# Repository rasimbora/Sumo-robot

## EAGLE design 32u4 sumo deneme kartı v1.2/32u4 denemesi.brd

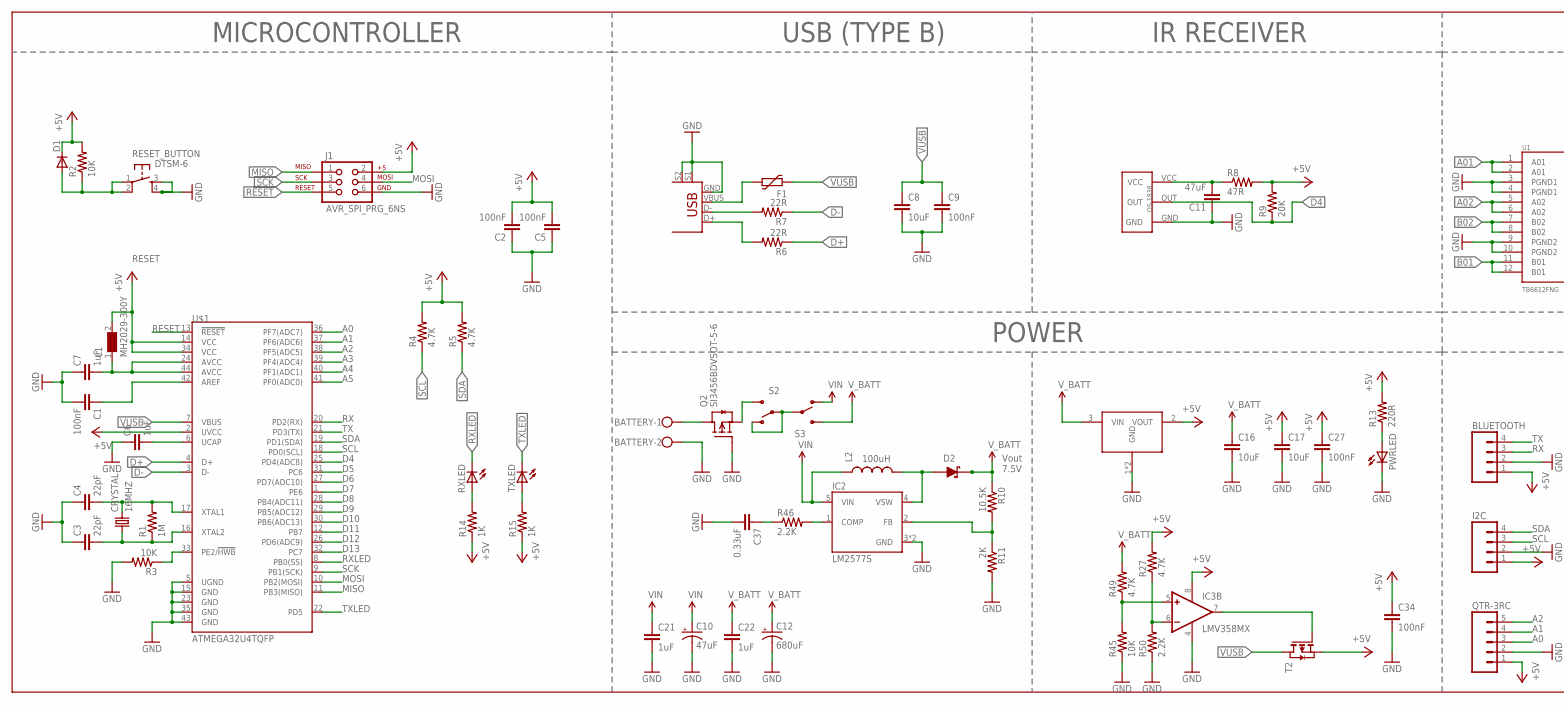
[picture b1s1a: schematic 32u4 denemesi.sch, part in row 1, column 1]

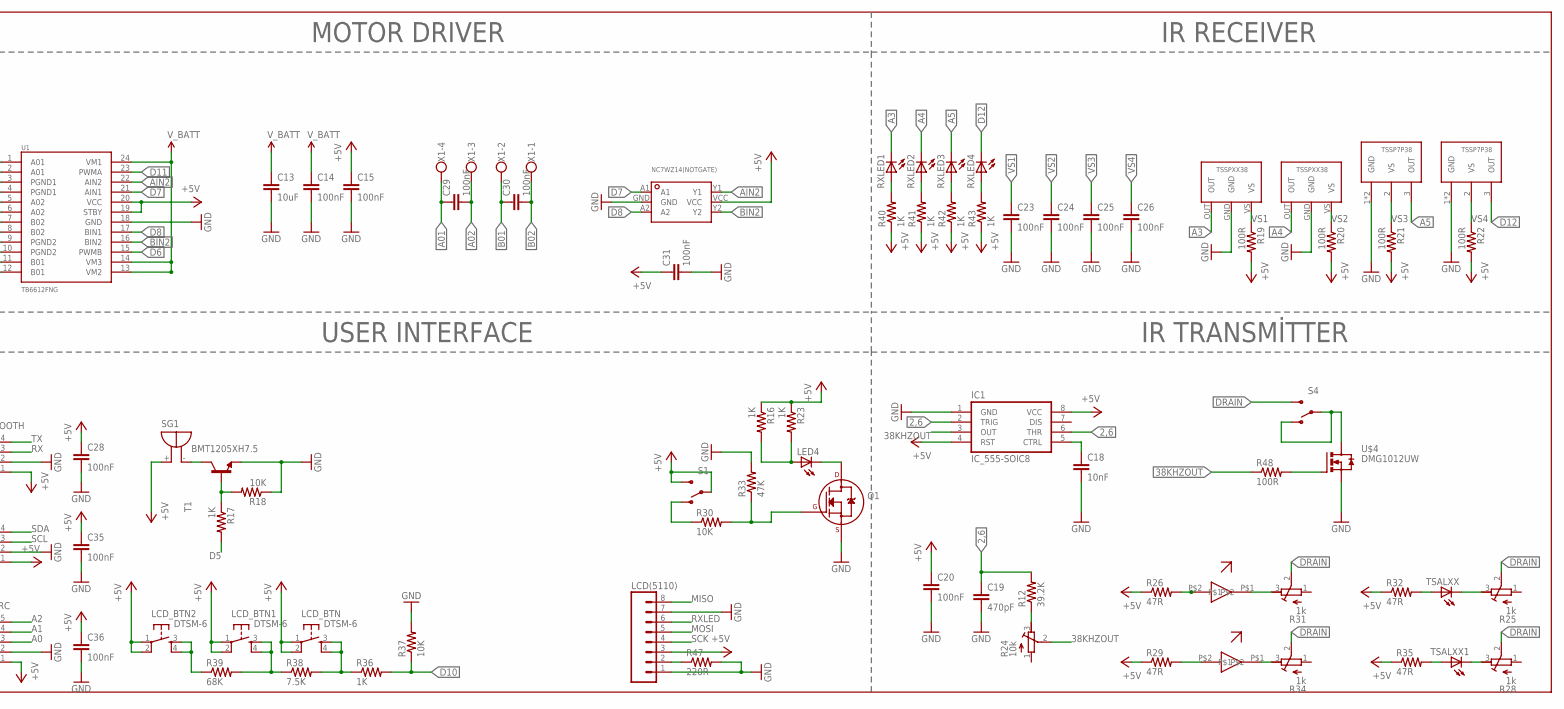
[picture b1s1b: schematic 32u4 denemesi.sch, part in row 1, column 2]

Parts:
BATTERY: W237-102
BLUETOOTH: M04PTH; 1X04
C1, C2, C5, C9, C14, C15, C20, C23, C24, C25, C26, C27, C28, C29, C30, C31, C34, C35, C36: 100nF; 1206
C3, C4: 22pF; 1206
C6, C7, C21, C22: 1uF; 1206
C8, C13, C16, C17: 10uF; 1206
C10: 47uF; NIPPON_F80
C11: 47uF; 1206
C12: 680uF; PANASONIC_G
C18: 10nF; 1206
C19: 470pF; 1206
C37: 0.33uF; 1206
CRYSTAL: 16MHZ; CRYSTAL-SMD-5X3
D1: DIODE-MINIMELF; MINIMELF
D2: D_SCHOTTKYA; SMA
F1: FUSE_PTC-0805; PTC0805
I2C: M04PTH; 1X04
IC1: IC_555-SOIC8; SOIC-8
IC2: LM2577S; TO263-5
IC3: LMV358MX; SO08
J1: AVR_SPI_PRG_6NS; 2X3-NS
L1: MH2029-300Y; 0805
L2: INDUCTORPWR; CDRH125
LCD(5110): M081X08; 1X08
LCD_BTN, LCD_BTN1, LCD_BTN2: DTSM-6
LED4: LEDCHIPLED_0805; CHIPLED_0805
PWRLED: LEDCHIPLED_0805; CHIPLED_0805
Q1: 2N7000_SOT23; SOT-23
Q2: SI3456BDVSOT-5-6; SOT23-6
QTR-3RC: M05PTH; 1X05
R1: 1M; 0805
R2, R3, R18, R30, R37, R45: 10K; 0805
R4, R5, R27, R49: 4.7K; 0805
R6, R7: 22R; 0805
R8, R26, R29, R32, R35: 47R; 0805
R9: 20K; 0805
R10: 10.5K; 0805
R11: 2K; 0805
R12: 39.2K; 0805
R13, R47: 220R; 0805
R14, R15, R16, R17, R23, R36, R40, R41, R42, R43: 1K; 0805
R19, R20, R21, R22, R48: 100R; 0805
R24: 10k; RTRIM3296W
R25, R28, R31, R34: 1k; RTRIM3296W
R33: 47K; 0805
R38: 7.5K; 0805
R39: 68K; 0805
R46, R50: 2.2K; 0805
RESET_BUTTON: DTSM-6
RXLED, RXLED1, RXLED2, RXLED3, RXLED4: LEDCHIPLED_0805; CHIPLED_0805
S1, S2, S3, S4: SWITCH-SPDTPTH; SWITCH-SPDT
SG1: BMT1205XH7.5
T1: MMBT2222ALT1-NPN-SOT23-BEC; SOT23-BEC
T2: PMOSSOT23; SOT-23
TSALXX, TSALXX1: LED5MM
TXLED: LEDCHIPLED_0805; CHIPLED_0805
U1: TB6612FNG; SSOP24
U$1: ATMEGA32U4TQFP; SPARKFUN-DIGITALIC_TQFP44
U$2: USB+SHIELD; USB-B-PTH
U$3: OS-1838
U$4: DMG1012UW; SOT323
U$5: NCP1117; SOT223
U$6, U$7: TSSP7P38
U$8, U$9: TSSPXX38
U$10: NC7WZ14(NOTGATE); SC-70-6
U$11, U$12: IRLED
X1: W237-4

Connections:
2,6: C19.1, IC1.2 (TRIG), IC1.6 (THR), R12.2
38KHZOUT: IC1.3 (OUT), R24.2 (S), R48.1
+5V: BLUETOOTH.1, C2.2, C5.2, C15.1, C17.1, C20.1, C27.1, C28.1, C31.1, C34.1, C35.1, C36.1, D1.C, I2C.1, IC1.4 (RST), IC1.8 (VCC), IC3.8 (V+), J1.2, L1.2, LCD(5110).3, LCD_BTN.1, LCD_BTN.2, LCD_BTN1.1, LCD_BTN1.2, LCD_BTN2.1, LCD_BTN2.2, QTR-3RC.1, R2.2, R4.2, R5.2, R8.2, R9.2, R13.2, R14.1, R15.1, R16.1, R19.2, R20.2, R21.2, R22.2, R23.1, R26.1, R27.2, R29.1, R32.1, R35.1, R40.1, R41.1, R42.1, R43.1, S1.2, S1.3 (S), SG1.+, T2.2 (S), U1.19 (STBY), U1.20 (VCC), U$1.2 (UVCC), U$1.14 (VCC), U$1.34 (VCC), U$5.2 (VOUT), U$10.VCC
A0: QTR-3RC.3, U$1.36 (PF7(ADC7))
A1: QTR-3RC.4, U$1.37 (PF6(ADC6))
A01: C29.1, U1.1 (A01), U1.2 (A01), X1.4
A2: QTR-3RC.5, U$1.38 (PF5(ADC5))
A02: C29.2, U1.5 (A02), U1.6 (A02), X1.3
A3: RXLED1.C, U$1.39 (PF4(ADC4)), U$9.OUT
A4: RXLED2.C, U$1.40 (PF1(ADC1)), U$8.OUT
A5: RXLED3.C, U$1.41 (PF0(ADC0)), U$6.3 (OUT)
AIN2: U1.22 (AIN2), U$10.Y1
B01: C30.1, U1.11 (B01), U1.12 (B01), X1.2
B02: C30.2, U1.7 (B02), U1.8 (B02), X1.1
BIN2: U1.16 (BIN2), U$10.Y2
CTRL: C18.1, IC1.5 (CTRL)
D4: R9.1, U$1.25 (PD4(ADC8)), U$3.OUT
D5: R17.2, U$1.31 (PC6)
D6: U1.15 (PWMB), U$1.27 (PD7(ADC10))
D7: U1.21 (AIN1), U$1.1 (PE6), U$10.A1
D8: U1.17 (BIN1), U$1.28 (PB4(ADC11)), U$10.A2
D9: U$1.29 (PB5(ADC12))
D10: R36.2, R37.1, U$1.30 (PB6(ADC13))
D11: U1.23 (PWMA), U$1.12 (PB7)
D12: RXLED4.C, U$1.26 (PD6(ADC9)), U$7.3 (OUT)
D13: U$1.32 (PC7)
D+: R6.1, U$1.4 (D+)
D-: R7.1, U$1.3 (D-)
DRAIN: R25.2 (S), R28.2 (S), R31.2 (S), R34.2 (S), S4.3 (S)
GND: BATTERY.2, BLUETOOTH.2, C1.2, C2.1, C3.1, C4.1, C5.1, C6.1, C7.1, C8.2, C9.2, C10.-, C11.1, C12.-, C13.2, C14.2, C15.2, C16.2, C17.2, C18.2, C19.2, C20.2, C21.2, C22.2, C23.2, C24.2, C25.2, C26.2, C27.2, C28.2, C31.2, C34.2, C35.2, C36.2, C37.2, I2C.2, IC1.1 (GND), IC2.3 (GND), IC2.6 (GND), IC3.4 (V-), J1.6, LCD(5110).1, LCD(5110).7, PWRLED.C, Q1.2 (S), Q2.3 (G), QTR-3RC.2, R3.2, R11.2, R18.1, R33.2, R37.2, R45.1, R47.2, R50.1, RESET_BUTTON.3, RESET_BUTTON.4, T1.E, U1.3 (PGND1), U1.4 (PGND1), U1.9 (PGND2), U1.10 (PGND2), U1.18 (GND), U$1.5 (UGND), U$1.15 (GND), U$1.23 (GND), U$1.35 (GND), U$1.43 (GND), U$2.GND, U$2.S1, U$2.S2, U$3.GND, U$4.2 (S), U$5.1 (GND), U$5.4 (GND), U$6.1 (GND), U$6.4 (GND), U$7.1 (GND), U$7.4 (GND), U$8.GND, U$9.GND, U$10.GND
MISO: J1.1, LCD(5110).8, U$1.11 (PB3(MISO))
MOSI: J1.4, LCD(5110).5, U$1.10 (PB2(MOSI))
unnamed: C7.2, L1.1, U$1.24 (AVCC), U$1.44 (AVCC)
unnamed: C1.1, U$1.42 (AREF)
unnamed: C6.2, U$1.6 (UCAP)
unnamed: C4.2, CRYSTAL.3 (2), R1.2, U$1.17 (XTAL1)
unnamed: C3.2, CRYSTAL.1, R1.1, U$1.16 (XTAL2)
unnamed: F1.2, U$2.VBUS
unnamed: R3.1, U$1.33 (PE2/!HWB)
unnamed: LCD_BTN2.3, LCD_BTN2.4, R39.1
unnamed: R7.2, U$2.D-
unnamed: R6.2, U$2.D+
unnamed: IC3.5 (+IN), R45.2, R49.1
unnamed: C11.2, R8.1, U$3.VCC
unnamed: PWRLED.A, R13.1
unnamed: IC2.2 (FB), R10.2, R11.1
unnamed: R48.2, U$4.1 (G)
unnamed: LCD_BTN.3, LCD_BTN.4, R36.1, R38.2
unnamed: LCD_BTN1.3, LCD_BTN1.4, R38.1, R39.2
unnamed: R40.2, RXLED1.A
unnamed: R14.2, RXLED.A
unnamed: R15.2, TXLED.A
unnamed: LED4.A, R16.2, R23.2
unnamed: R17.1, R18.2, T1.B
unnamed: IC3.6 (-IN), R27.1, R50.2
unnamed: SG1.-, T1.C
unnamed: IC3.7 (OUT), T2.3 (G)
unnamed: R12.1, R24.3 (A)
unnamed: R41.2, RXLED2.A
unnamed: S4.1 (O), S4.2, U$4.3 (D)
unnamed: R25.3 (A), TSALXX.K (C)
unnamed: R32.2, TSALXX.A
unnamed: LED4.C, Q1.3 (D)
unnamed: R28.3 (A), TSALXX1.K (C)
unnamed: R35.2, TSALXX1.A
unnamed: R30.1, S1.1 (O)
unnamed: Q1.1 (G), R30.2, R33.1
unnamed: R31.3 (A), U$11.P$1
unnamed: R26.2, U$11.P$2
unnamed: R34.3 (A), U$12.P$1
unnamed: R29.2, U$12.P$2
unnamed: BATTERY.1, Q2.1 (D), Q2.2 (D), Q2.5 (D), Q2.6 (D)
unnamed: R42.2, RXLED3.A
unnamed: Q2.4 (S), S2.3 (S)
unnamed: IC2.1 (COMP), R46.2
unnamed: C37.1, R46.1
unnamed: S2.1 (O), S2.2, S3.2
unnamed: LCD(5110).2, R47.1
unnamed: R43.2, RXLED4.A
RESET: D1.A, J1.5, R2.1, RESET_BUTTON.1, RESET_BUTTON.2, U$1.13 (!RESET)
RX: BLUETOOTH.3, U$1.20 (PD2(RX))
RXLED: LCD(5110).6, RXLED.C, U$1.8 (PB0(SS))
SCK: J1.3, LCD(5110).4, U$1.9 (PB1(SCK))
SCL: I2C.3, R4.1, U$1.18 (PD0(SCL))
SDA: I2C.4, R5.1, U$1.19 (PD1(SDA))
TX: BLUETOOTH.4, U$1.21 (PD3(TX))
TXLED: TXLED.C, U$1.22 (PD5)
VIN: C10.+, C21.1, IC2.5 (VIN), L2.1, S3.1 (O)
VS1: C23.1, R19.1, U$9.VS
VS2: C24.1, R20.1, U$8.VS
VS3: C25.1, R21.1, U$6.2 (VS)
VS4: C26.1, R22.1, U$7.2 (VS)
VSW: D2.2 (A), IC2.4 (VSW), L2.2
VUSB: C8.1, C9.1, F1.1, T2.1 (D), U$1.7 (VBUS)
V_BATT: C12.+, C13.1, C14.1, C16.1, C22.1, D2.1 (C), R10.1, R49.2, S3.3 (S), U1.13 (VM2), U1.14 (VM3), U1.24 (VM1), U$5.3 (VIN)

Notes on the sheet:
MICROCONTROLLER
USB (TYPE B)
POWER
IR RECEIVER
MOTOR DRIVER
USER INTERFACE
IR TRANSMİTTER
Vout 7.5V
100uH

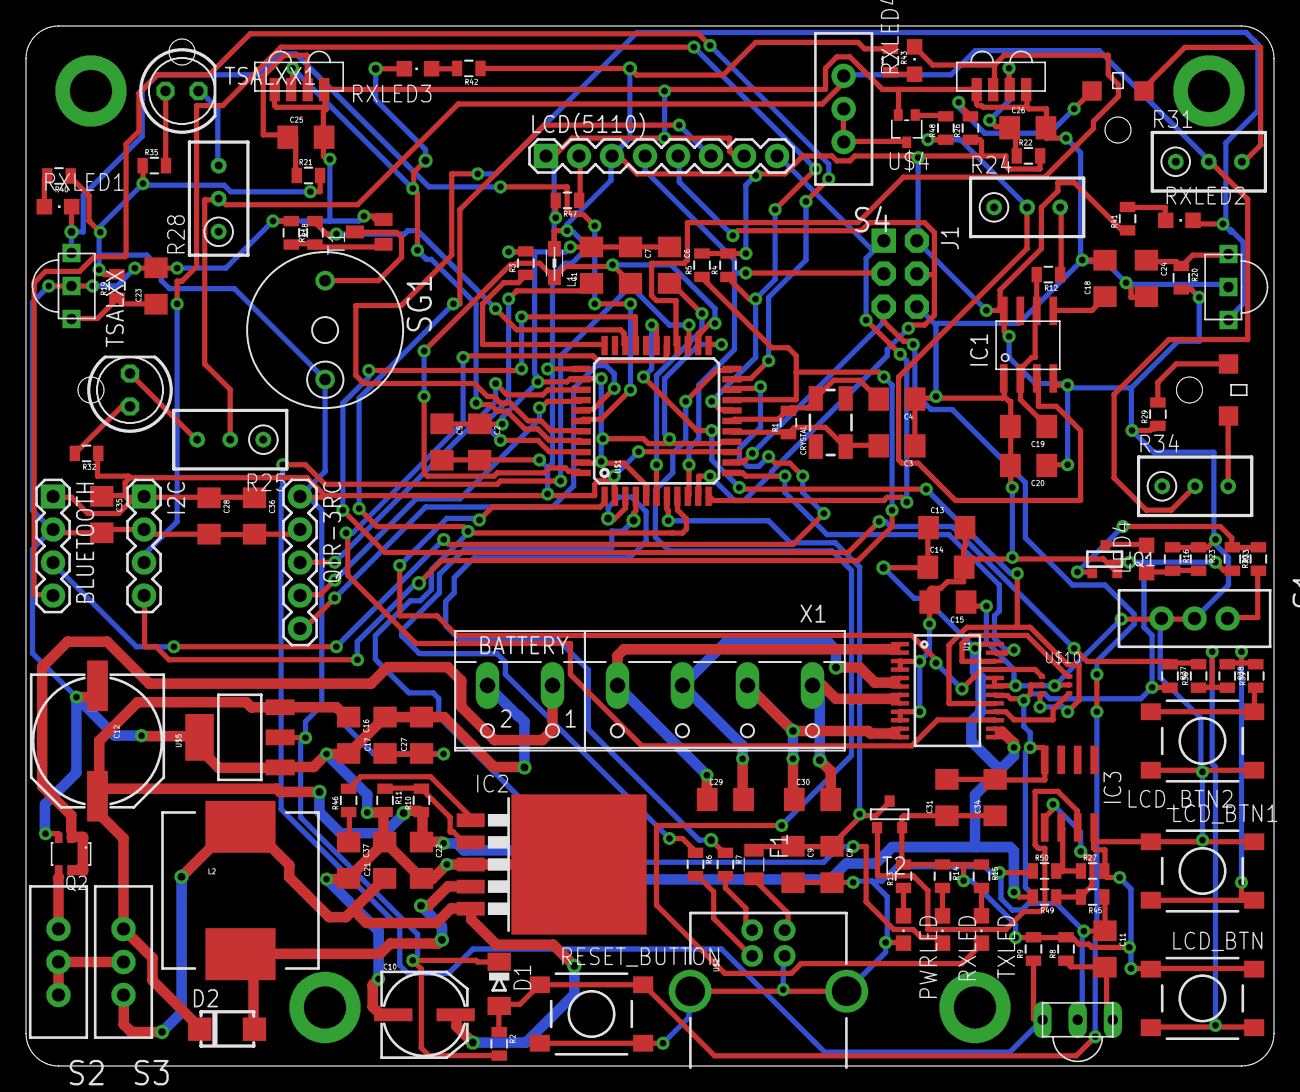
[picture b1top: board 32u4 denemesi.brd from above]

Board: 2 copper layers, 96.0 x 80.0 mm, 136 parts (0 on the bottom side), 93 nets.

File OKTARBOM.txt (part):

Partlist exported from C:/Users/rasim/Desktop/32u4 sumo deneme kartý v1.2/32u4 denemesi.sch at 2.08.2016 18:44

Qty Value            Device                     Package                   Parts                                                                                     Description                                                                            MF MPN     OC_FARNELL OC_NEWARK PROD_ID  VALUE    
1                    2N7000_SOT23               SOT-23                    Q1                                                                                        2N7000, 2N7002, NDS7002A                                                                                                                 
1                    *DIODE-MINIMELF             MINIMELF                  D1                                                                                        DIODE                                                                                                                                    
1                    D_SCHOTTKYA                SMA                       D2                                                                                        Schottky diodes in various packages                                                                                                      
1                    *FUSE_PTC-0805              PTC0805                   F1                                                                                        Resettable PTC                                                                                                                           
1                    INDUCTORPWR                CDRH125                   L2                                                                                        Inductors                                                                                                                                
2                    *LED5MM                     LED5MM                    TSALXX, TSALXX1                                                                           LED                                                                                                                                      
8                    *LEDCHIPLED_0805            CHIPLED_0805              LED4, PWRLED, RXLED, RXLED1, RXLED2, RXLED3, RXLED4, TXLED                                LED                                                                                                                                      
2                    *M04PTH                     1X04                      BLUETOOTH, I2C                                                                            Header 4                                                                                                                                 
1                    *M05PTH                     1X05                      QTR-3RC                                                                                   Header 5                                                                                                                                 
1                    *M081X08                    1X08                      LCD(5110)                                                                                 Header 8                                                                                                                                 
1                    *MMBT2222ALT1-NPN-SOT23-BEC SOT23-BEC                 T1                                                                                        NPN Transistror                                                                                                                          
1                    *PMOSSOT23                  SOT-23                    T2                                                                                        MOS FET                                                                                           unknown    unknown                     
4                    *SWITCH-SPDTPTH             SWITCH-SPDT               S1, S2, S3, S4                                                                            SPDT Switch                                                                                                                              
1                    *W237-102                   W237-102                  BATTERY                                                                                   WAGO SCREW CLAMP                                                                          237-102 unknown    70K9898                     
1                    *W237-4                     W237-4                    X1                                                                                        WAGO SCREW CLAMP                                                                                  unknown    unknown                     
1   0.33uF           -CAP1206                    1206                      C37                                                                                       Capacitor                                                                                                                                
1   10.5K            -RESISTOR0805-RES           0805                      R10                                                                                       Resistor                                                                                                                                 
5   100R             *RESISTOR0805-RES           0805                      R19, R20, R21, R22, R48                                                                   Resistor                                                                                                                                 
19  100nF            -805-CAP1206                    1206                      C1, C2, C5, C9, C14, C15, C20, C23, C24, C25, C26, C27, C28, C29, C30, C31, C34, C35, C36 Capacitor                                                                                                                                
6   10K              *RESISTOR0805-RES           0805                      R2, R3, R18, R30, R37, R45                                                                Resistor                                                                                                                                 
1   10k              *R-TRIMM3296W               RTRIM3296W                R24                                                                                       Trimm resistor                                                                                                                           
1   10nF             -805-CAP1206                    1206                      C18                                                                                       Capacitor                                                                                                                                
4   10uF             -805-CAP1206                    1206                      C8, C13, C16, C17                                                                         Capacitor                                                                                                                                
1   16MHZ            *CRYSTAL5X3                 CRYSTAL-SMD-5X3           CRYSTAL                                                                                   Various standard crystals. Proven footprints. Spark Fun Electronics SKU : COM-00534                                                      
10  1K               *RESISTOR0805-RES           0805                      R14, R15, R16, R17, R23, R36, R40, R41, R42, R43                                          Resistor                                                                                                                                 
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
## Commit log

2016-08-02 :boom::camel: Added .gitattributes & .gitignore files
2016-08-02 ver1.0
2016-08-02 ver1.1
2016-08-02 ver1.3
2016-08-02 ver1.4
2016-08-02 çizimler eklendi
2016-08-02 Oktar Malzemelere Baktı

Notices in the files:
parts and their libraries:
SparkFun-DigitalIC: Licensing: CC v3.0 Share-Alike You are welcome to use this library for commercial purposes.
wuerth_elektronik_v5: Copyright: Würth Elektronik eiSos
m-pad-2.1: License : GNU General Public License version 2 (see bottom)
